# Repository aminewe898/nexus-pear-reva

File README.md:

# NEXUS PEAR REV A — pear pressure

**DO NOT ORDER — engineering review submission.** Revised project: 2026-10-07.

ESP32-S3-WROOM-1U-N16R8, 16 MB flash/8 MB PSRAM, Waveshare 29318 IPS touch display (320 x 480 native / 480 x 320 landscape), two-point FT6336U, digital I2S microphone, stereo MAX98357A modules, 8-ohm speakers, optional microSD, real U.FL-to-RP-SMA external antenna, six ADC keys and bottom USB-C. Carrier 100 x 90 mm, four layers, no battery. Design peak allowance 11.54 W including 20% contingency and an enforced 0.75 W/channel audio cap; no measured peak is claimed.

Open hardware/kicad/nexus-pear-reva/nexus-pear-reva.kicad_pro in KiCad 10. Native schematic, PCB, local symbols and local footprints are included. previews/schematic.pdf is the complete eleven-sheet schematic; previews/pcb-layers.pdf and board-3d.png support review. Manufacturing Gerbers, Excellon drill files, placement CSV, BOM and STEP are under hardware/manufacturing/. Do not submit those as an approved fabrication order.

hardware/BOM_REVA.csv contains exact candidate MPNs; hardware/RFQ_GROUPED.csv groups quantities for procurement. Pricing is incomplete. SUBMISSION.md is the short cover note; docs/ contains the architecture, processor comparison, display/audio/power calculations, pin map, footprint review, sources and first-article test plan. docs/DESIGN_REVIEW_REVA.md identifies every remaining release gate. Native ERC/DRC reports, pad inventory, route metrics and hashed delivery manifest are under validation/.

The revised circuit adds hardware Type-C current qualification and protected input power, removes independently powered 3.3 V peripherals, isolates audio signals and replaces the undocumented display. Corrected manufacturer footprints and routing are in this project's native files. Firmware, physical qualification, complete procurement and enclosure design remain to be completed.

## Publication check — 2026-10-10

A quick source/history credential-pattern scan found no obvious credentials. The delivery manifest was checked against the current checkout: 81 of 84 recorded files match their hashes. The KiCad project file, manufacturing STEP file, and `validation/bom-summary.json` differ from the recorded manifest. This indicates a stale or inconsistent delivery record; those artifacts need reconciliation before release. No CAD regeneration, electrical validation, fabrication approval, or bench testing was performed in this check. The **DO NOT ORDER** status remains in force.

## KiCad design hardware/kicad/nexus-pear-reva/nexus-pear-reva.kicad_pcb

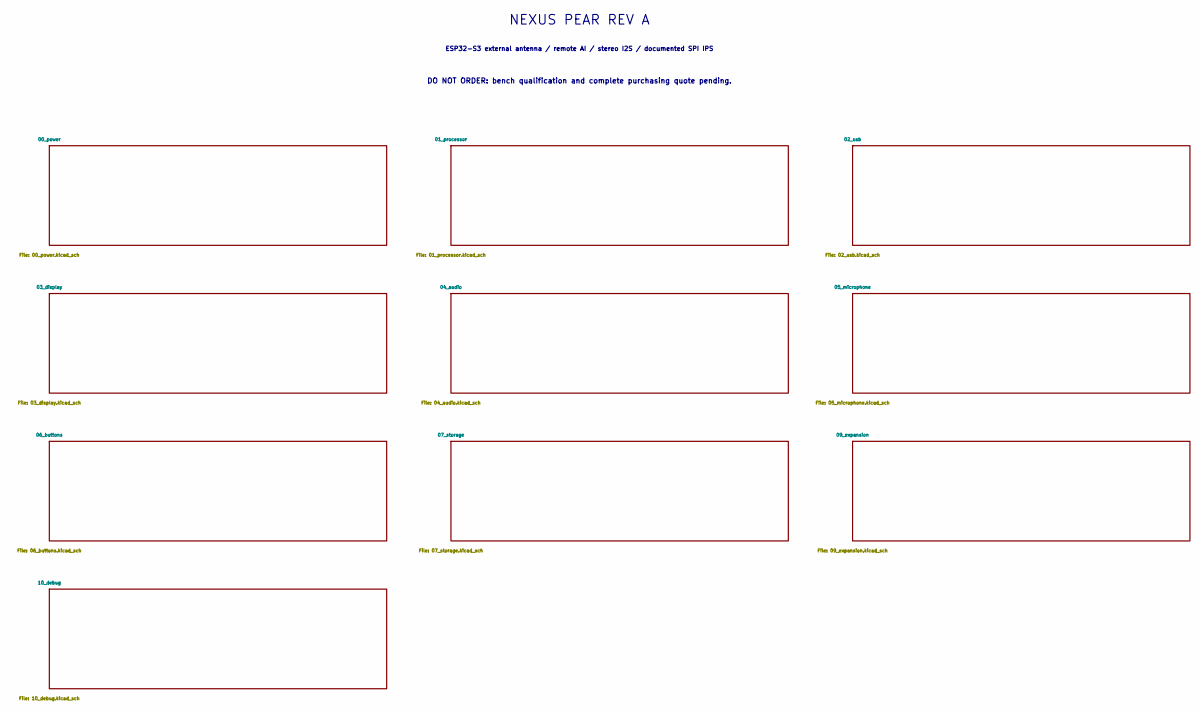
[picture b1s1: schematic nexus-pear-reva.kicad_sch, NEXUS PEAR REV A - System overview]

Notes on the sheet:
NEXUS PEAR REV A
ESP32-S3 external antenna / remote AI / stereo I2S / documented SPI IPS
DO NOT ORDER: bench qualification and complete purchasing quote pending.

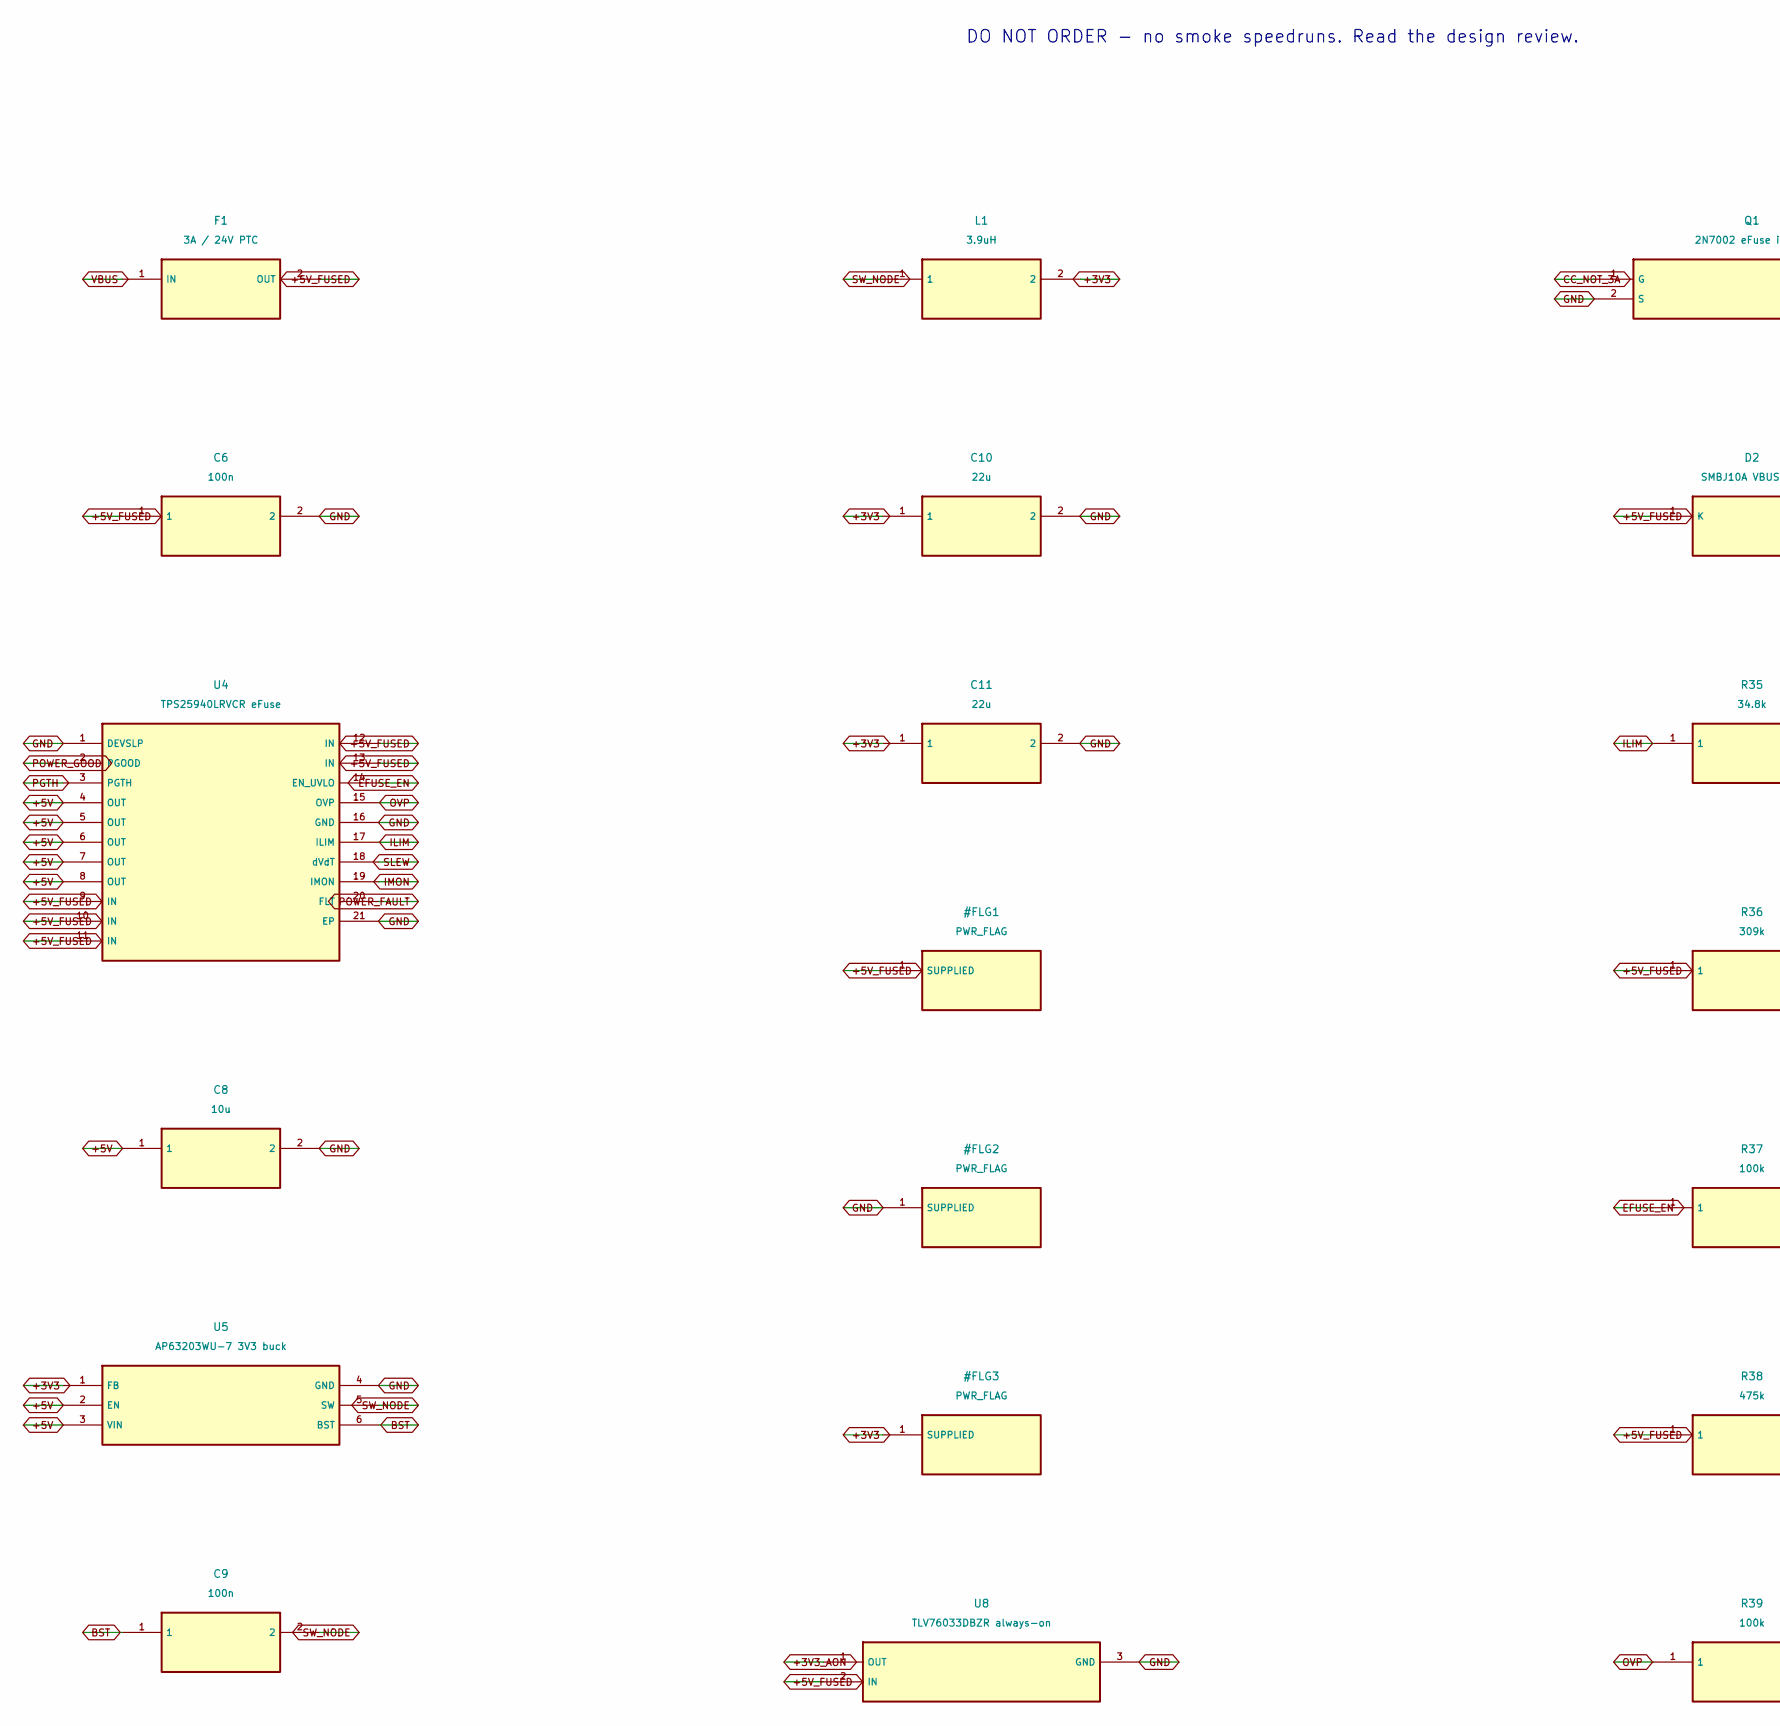
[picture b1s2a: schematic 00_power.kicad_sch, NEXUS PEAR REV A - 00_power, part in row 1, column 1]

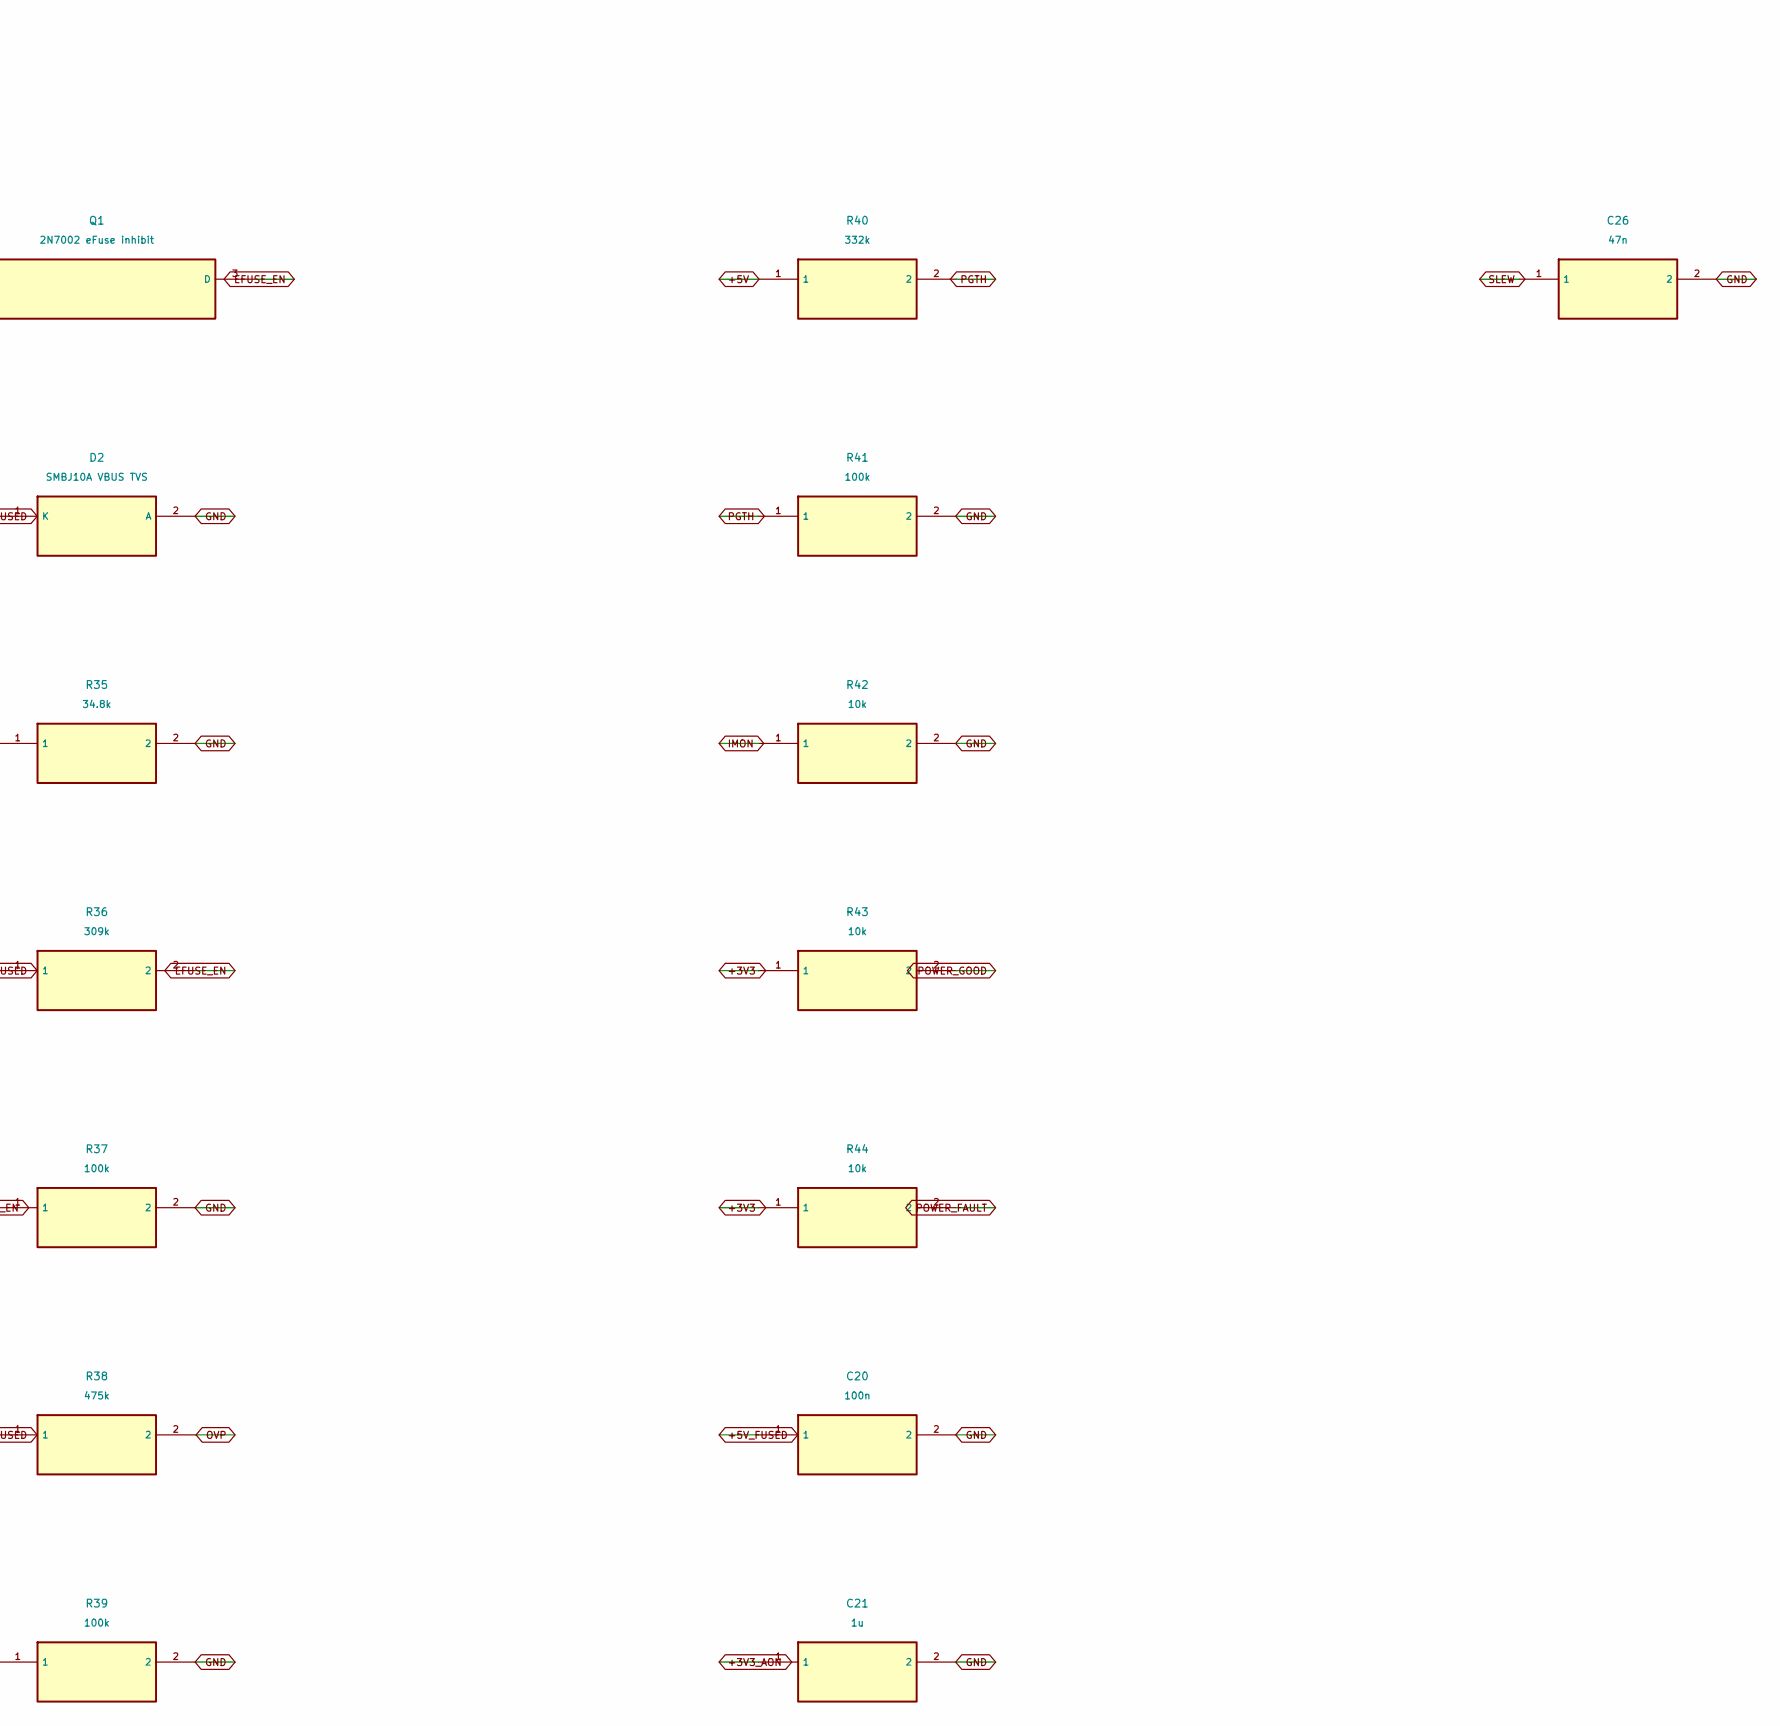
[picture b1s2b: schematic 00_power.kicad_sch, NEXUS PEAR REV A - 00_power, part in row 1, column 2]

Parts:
C6, C9, C20: 100n; C_0805_2012Metric; MPN GRM21BR71H104KA01L
C8: 10u; C_1206_3216Metric; MPN GRM31CR61A106KA01L
C10, C11: 22u; C_1206_3216Metric; MPN GRM31CR61A226KE19L
C21: 1u; C_0805_2012Metric; MPN GRM21BR71A105KA01L
C26: 47n; C_0805_2012Metric; MPN GRM21BR71H473KA01L
D2: SMBJ10A VBUS TVS; D_SMB; MPN SMBJ10A
F1: 3A / 24V PTC; Fuse_1812_4532Metric; MPN 1812L300/24SLER
L1: 3.9uH; L_Bourns-SRN6028; MPN SRN6028C-3R9M
Q1: 2N7002 eFuse inhibit; SOT-23; MPN 2N7002,215
R35: 34.8k; R_0805_2012Metric; MPN RC0805FR-0734K8L
R36: 309k; R_0805_2012Metric; MPN RC0805FR-07309KL
R37, R41: 100k; R_0805_2012Metric; MPN RC0805FR-07100KL
R38: 475k; R_0805_2012Metric; MPN RT0805BRD07475KL
R39: 100k; R_0805_2012Metric; MPN RT0805BRD07100KL
R40: 332k; R_0805_2012Metric; MPN RC0805FR-07332KL
R42, R43, R44: 10k; R_0805_2012Metric; MPN RC0805FR-0710KL
U4: TPS25940LRVCR eFuse; Texas_RVC0020A_WQFN-20-1EP_3x4mm_P0.5mm_EP1.6x2.6mm; MPN TPS25940LRVCR
U5: AP63203WU-7 3V3 buck; TSOT-23-6; MPN AP63203WU-7
U8: TLV76033DBZR always-on; SOT-23; MPN TLV76033DBZR

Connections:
+3V3: C10.1, C11.1, L1.2, R43.1, R44.1, U5.1 (FB); also elsewhere on the board
+3V3_AON: C21.1, U8.1 (OUT); also elsewhere on the board
+5V: C8.1, R40.1, U4.4 (OUT), U4.5 (OUT), U4.6 (OUT), U4.7 (OUT), U4.8 (OUT), U5.2 (EN), U5.3 (VIN); also elsewhere on the board
+5V_FUSED: C6.1, C20.1, D2.1 (K), F1.2 (OUT), R36.1, R38.1, U4.9 (IN), U4.10 (IN), U4.11 (IN), U4.12 (IN), U4.13 (IN), U8.2 (IN); also elsewhere on the board
BST: C9.1, U5.6 (BST)
CC_NOT_3A: Q1.1 (G); also elsewhere on the board
EFUSE_EN: Q1.3 (D), R36.2, R37.1, U4.14 (EN_UVLO)
GND: C6.2, C8.2, C10.2, C11.2, C20.2, C21.2, C26.2, D2.2 (A), Q1.2 (S), R35.2, R37.2, R39.2, R41.2, R42.2, U4.1 (DEVSLP), U4.16 (GND), U4.21 (EP), U5.4 (GND), U8.3 (GND); also elsewhere on the board
ILIM: R35.1, U4.17 (ILIM)
IMON: R42.1, U4.19 (IMON); also elsewhere on the board
OVP: R38.2, R39.1, U4.15 (OVP)
PGTH: R40.2, R41.1, U4.3 (PGTH)
POWER_FAULT: R44.2, U4.20 (FLT)
POWER_GOOD: R43.2, U4.2 (PGOOD)
SLEW: C26.1, U4.18 (dVdT)
SW_NODE: C9.2, L1.1, U5.5 (SW)
VBUS: F1.1 (IN); also elsewhere on the board

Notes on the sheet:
DO NOT ORDER - no smoke speedruns. Read the design review.

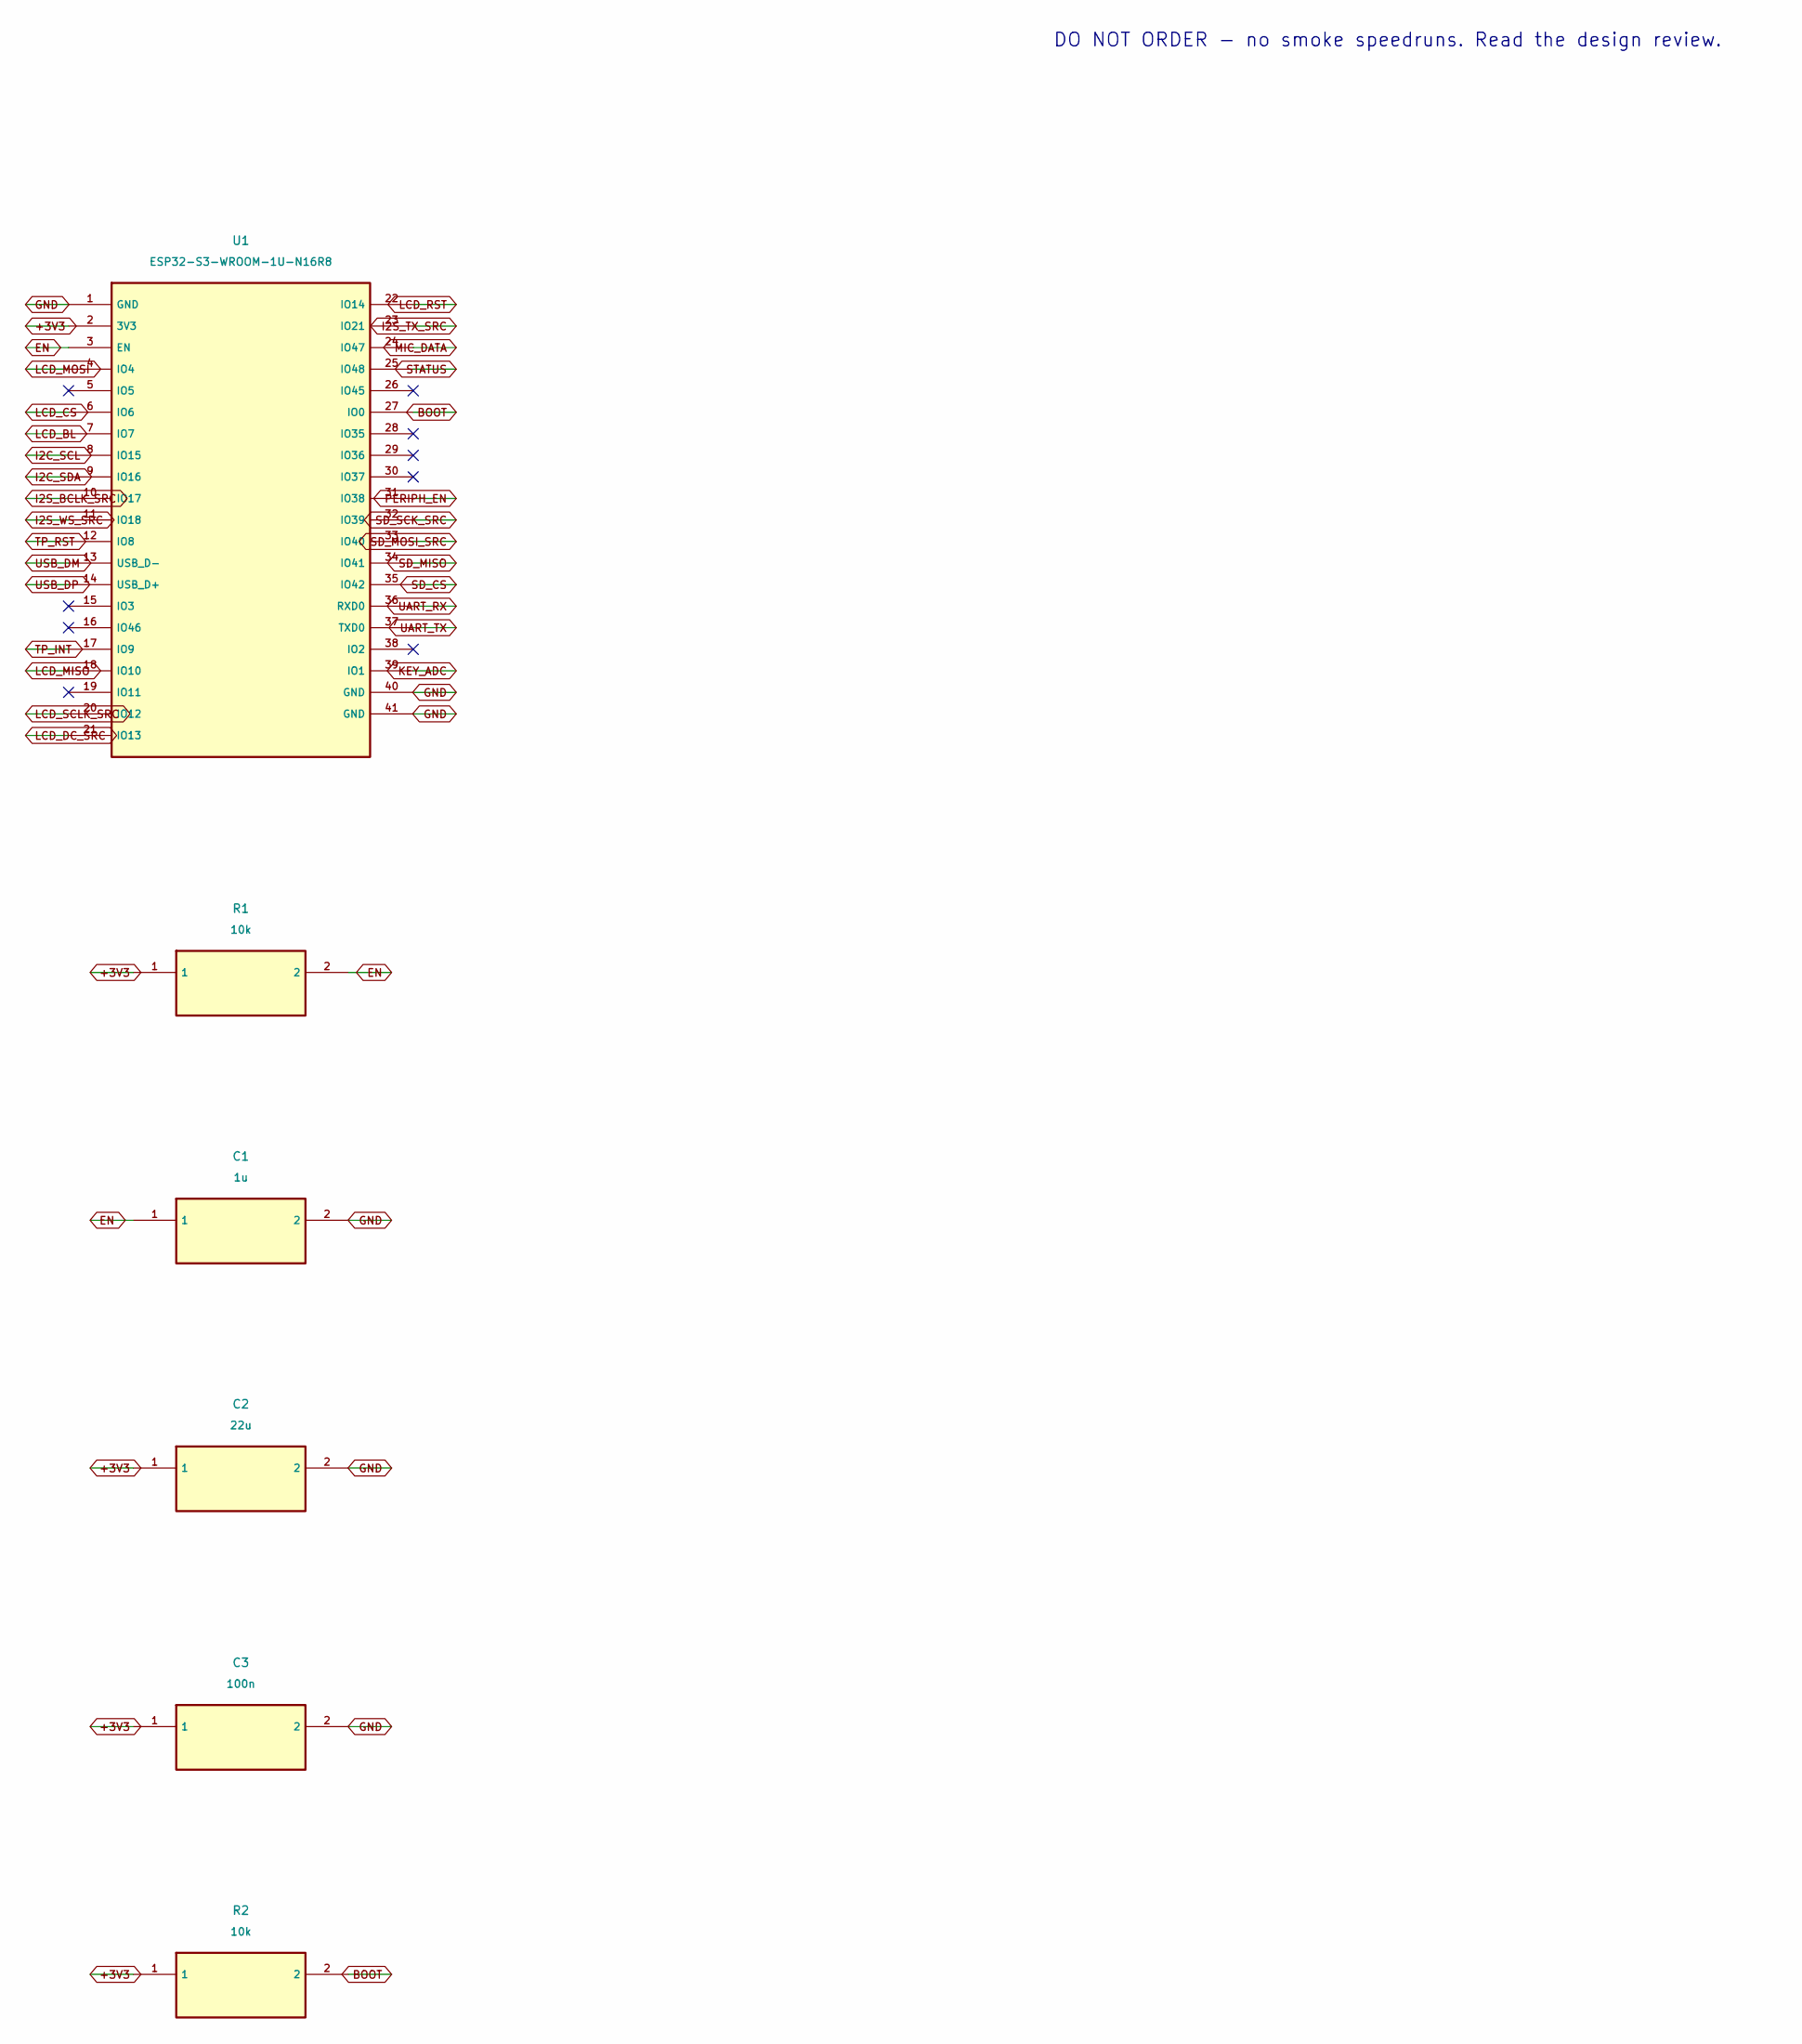
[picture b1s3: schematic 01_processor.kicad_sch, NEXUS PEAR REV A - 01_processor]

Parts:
C1: 1u; C_0805_2012Metric; MPN GRM21BR71A105KA01L
C2: 22u; C_1206_3216Metric; MPN GRM31CR61A226KE19L
C3: 100n; C_0805_2012Metric; MPN GRM21BR71H104KA01L
R1, R2: 10k; R_0805_2012Metric; MPN RC0805FR-0710KL
U1: ESP32-S3-WROOM-1U-N16R8; ESP32-S3-WROOM-1U; MPN ESP32-S3-WROOM-1U-N16R8

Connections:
+3V3: C2.1, C3.1, R1.1, R2.1, U1.2 (3V3); also elsewhere on the board
BOOT: R2.2, U1.27 (IO0); also elsewhere on the board
EN: C1.1, R1.2, U1.3 (EN); also elsewhere on the board
GND: C1.2, C2.2, C3.2, U1.1 (GND), U1.40 (GND), U1.41 (GND); also elsewhere on the board
I2C_SCL: U1.8 (IO15); also elsewhere on the board
I2C_SDA: U1.9 (IO16); also elsewhere on the board
I2S_BCLK_SRC: U1.10 (IO17); also elsewhere on the board
I2S_TX_SRC: U1.23 (IO21); also elsewhere on the board
I2S_WS_SRC: U1.11 (IO18); also elsewhere on the board
KEY_ADC: U1.39 (IO1); also elsewhere on the board
LCD_BL: U1.7 (IO7); also elsewhere on the board
LCD_CS: U1.6 (IO6); also elsewhere on the board
LCD_DC_SRC: U1.21 (IO13); also elsewhere on the board
LCD_MISO: U1.18 (IO10); also elsewhere on the board
LCD_MOSI: U1.4 (IO4); also elsewhere on the board
LCD_RST: U1.22 (IO14); also elsewhere on the board
LCD_SCLK_SRC: U1.20 (IO12); also elsewhere on the board
MIC_DATA: U1.24 (IO47); also elsewhere on the board
PERIPH_EN: U1.31 (IO38); also elsewhere on the board
SD_CS: U1.35 (IO42); also elsewhere on the board
SD_MISO: U1.34 (IO41); also elsewhere on the board
SD_MOSI_SRC: U1.33 (IO40); also elsewhere on the board
SD_SCK_SRC: U1.32 (IO39); also elsewhere on the board
STATUS: U1.25 (IO48); also elsewhere on the board
TP_INT: U1.17 (IO9); also elsewhere on the board
TP_RST: U1.12 (IO8); also elsewhere on the board
UART_RX: U1.36 (RXD0); also elsewhere on the board
UART_TX: U1.37 (TXD0); also elsewhere on the board
USB_DM: U1.13 (USB_D-); also elsewhere on the board
USB_DP: U1.14 (USB_D+); also elsewhere on the board

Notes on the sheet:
DO NOT ORDER - no smoke speedruns. Read the design review.

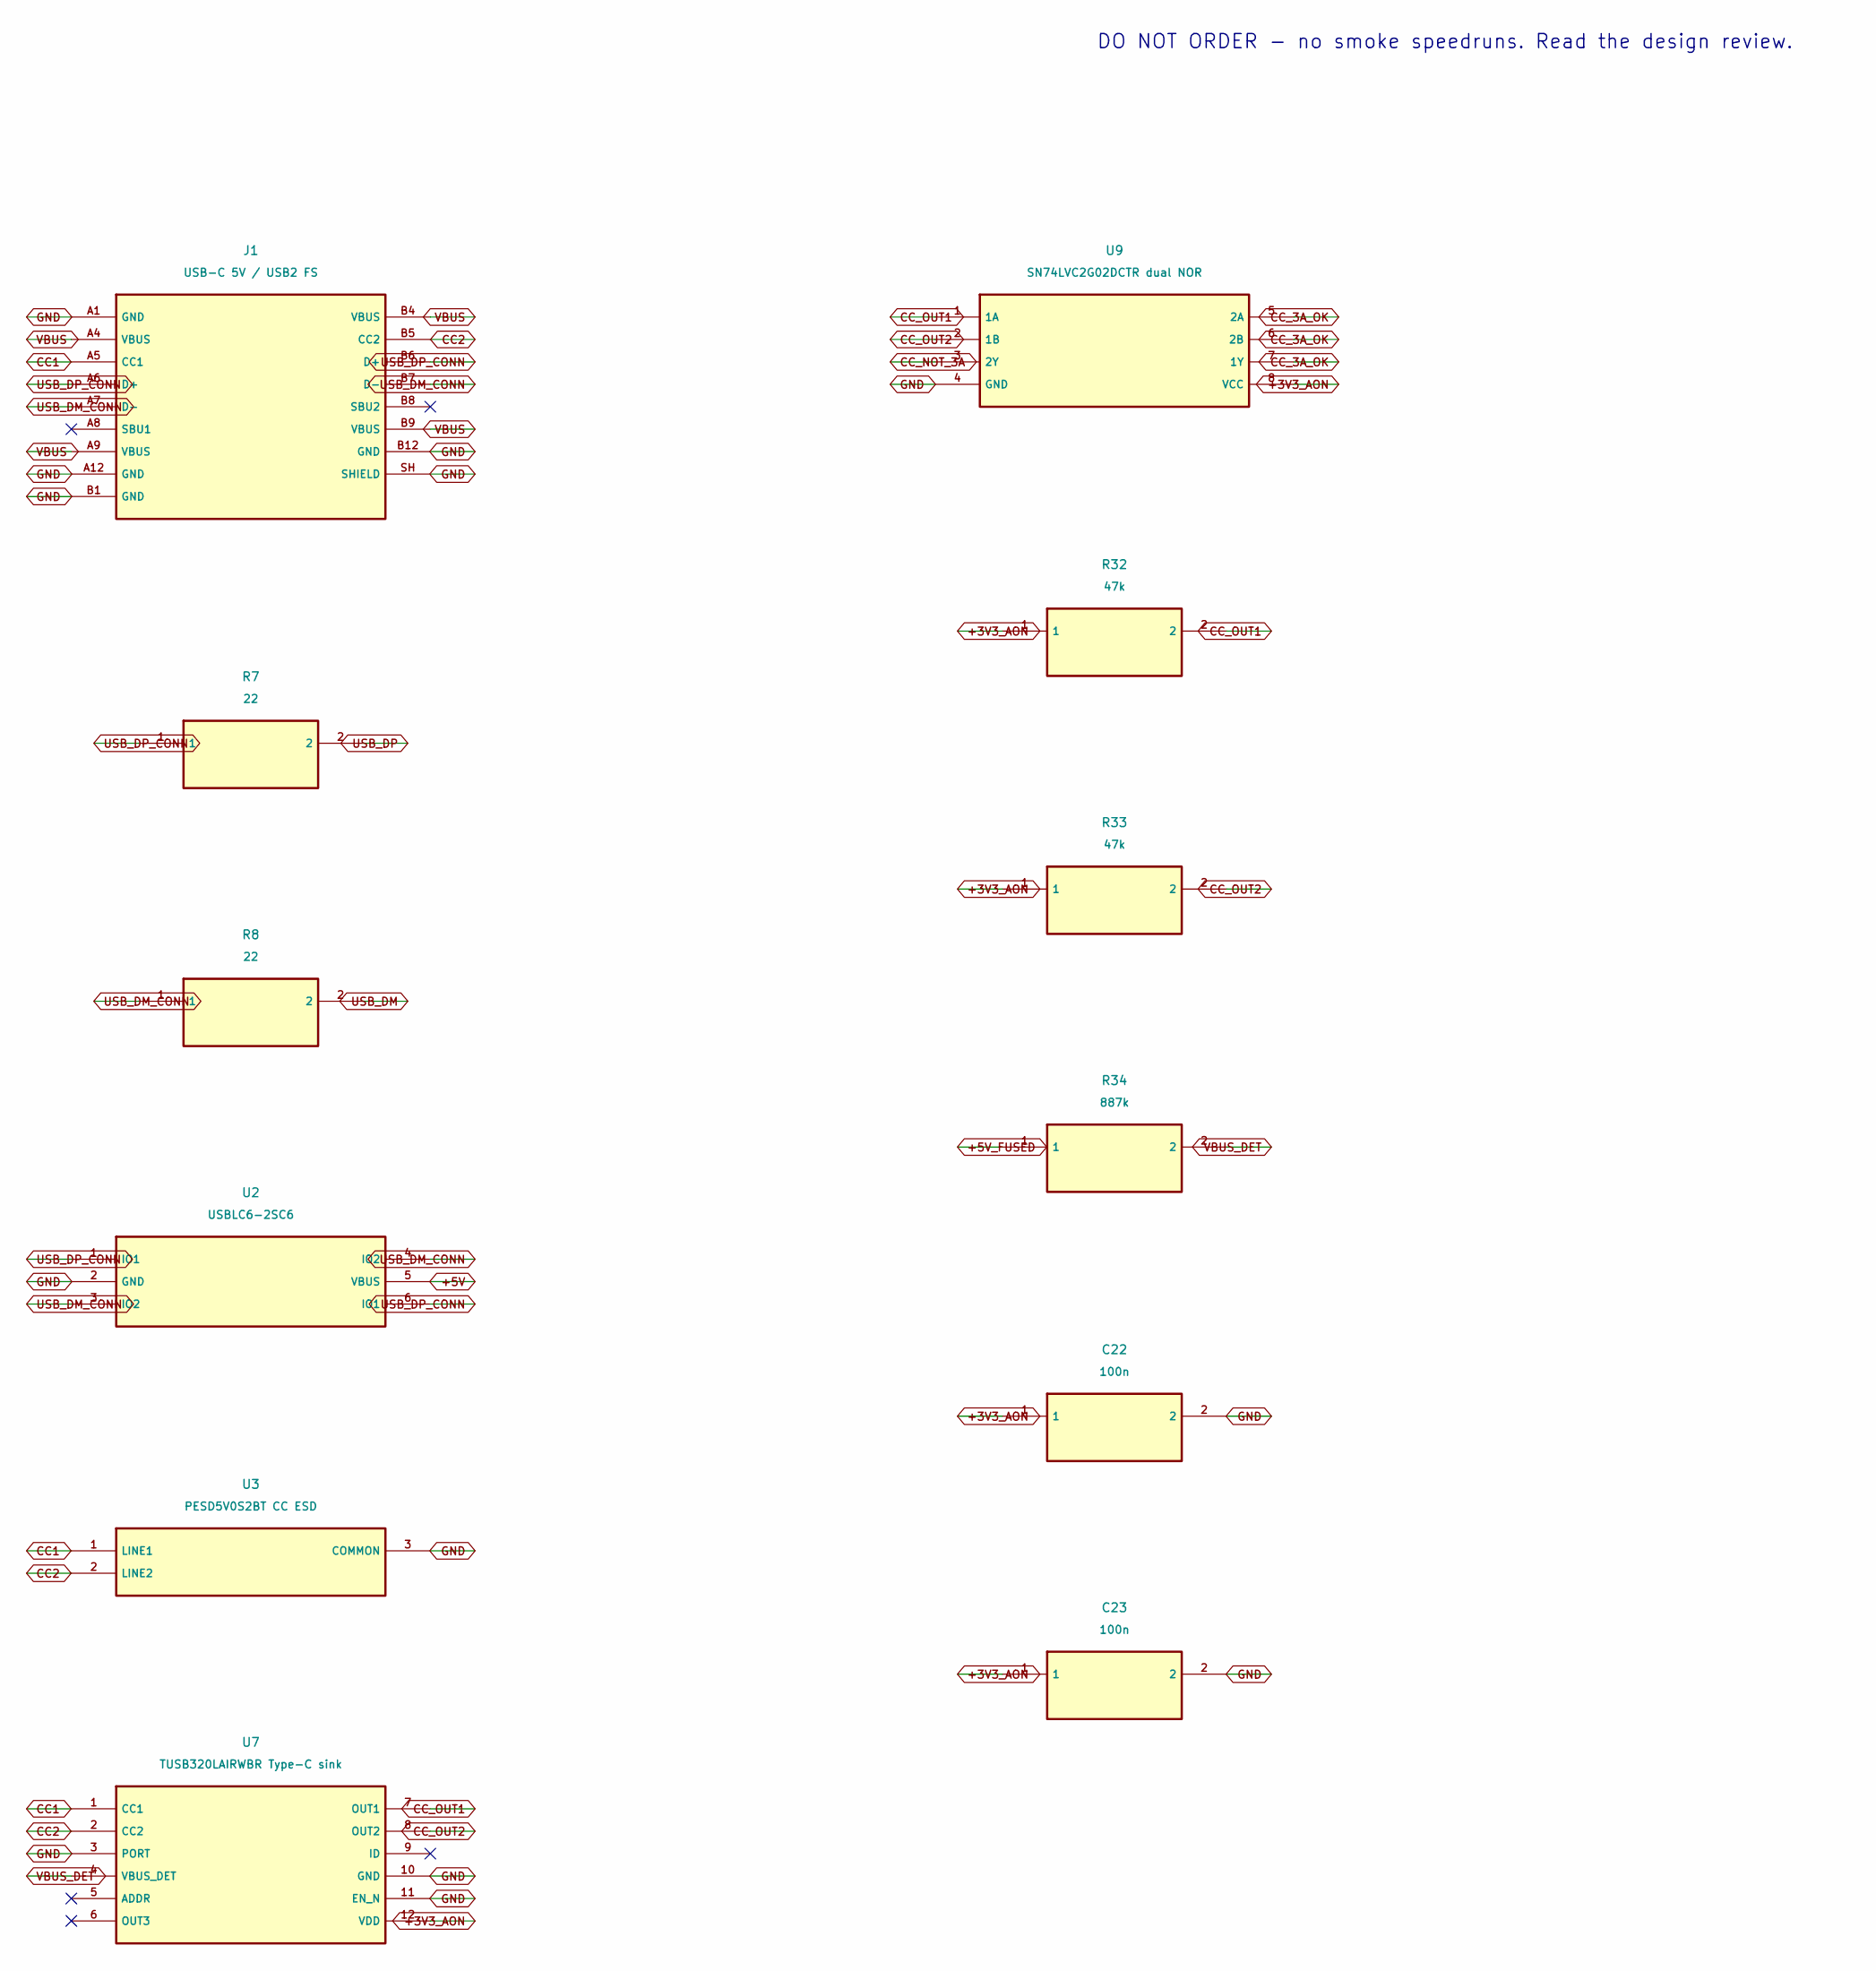
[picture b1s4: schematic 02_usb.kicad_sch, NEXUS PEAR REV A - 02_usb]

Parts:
C22, C23: 100n; C_0805_2012Metric; MPN GRM21BR71H104KA01L
J1: USB-C 5V / USB2 FS; USB_C_Receptacle_GCT_USB4105-xx-A_16P_TopMnt_Horizontal; MPN USB4105-GF-A
R7, R8: 22; R_0805_2012Metric; MPN RC0805FR-0722RL
R32, R33: 47k; R_0805_2012Metric; MPN RC0805FR-0747KL
R34: 887k; R_0805_2012Metric; MPN RC0805FR-07887KL
U2: USBLC6-2SC6; SOT-23-6; MPN USBLC6-2SC6
U3: PESD5V0S2BT CC ESD; SOT-23; MPN PESD5V0S2BT,215
U7: TUSB320LAIRWBR Type-C sink; Texas_X2QFN-12_1.6x1.6mm_P0.4mm; MPN TUSB320LAIRWBR
U9: SN74LVC2G02DCTR dual NOR; SSOP-8_2.95x2.8mm_P0.65mm; MPN SN74LVC2G02DCTR

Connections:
+3V3_AON: C22.1, C23.1, R32.1, R33.1, U7.12 (VDD), U9.8 (VCC); also elsewhere on the board
+5V: U2.5 (VBUS); also elsewhere on the board
+5V_FUSED: R34.1; also elsewhere on the board
CC1: J1.A5 (CC1), U3.1 (LINE1), U7.1 (CC1)
CC2: J1.B5 (CC2), U3.2 (LINE2), U7.2 (CC2)
CC_3A_OK: U9.5 (2A), U9.6 (2B), U9.7 (1Y); also elsewhere on the board
CC_NOT_3A: U9.3 (2Y); also elsewhere on the board
CC_OUT1: R32.2, U7.7 (OUT1), U9.1 (1A)
CC_OUT2: R33.2, U7.8 (OUT2), U9.2 (1B)
GND: C22.2, C23.2, J1.A1 (GND), J1.A12 (GND), J1.B1 (GND), J1.B12 (GND), J1.SH (SHIELD), U2.2 (GND), U3.3 (COMMON), U7.3 (PORT), U7.10 (GND), U7.11 (EN_N), U9.4 (GND); also elsewhere on the board
USB_DM: R8.2; also elsewhere on the board
USB_DM_CONN: J1.A7 (D-), J1.B7 (D-), R8.1, U2.3 (IO2), U2.4 (IO2)
USB_DP: R7.2; also elsewhere on the board
USB_DP_CONN: J1.A6 (D+), J1.B6 (D+), R7.1, U2.1 (IO1), U2.6 (IO1)
VBUS: J1.A4 (VBUS), J1.A9 (VBUS), J1.B4 (VBUS), J1.B9 (VBUS); also elsewhere on the board
VBUS_DET: R34.2, U7.4 (VBUS_DET)

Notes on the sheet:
DO NOT ORDER - no smoke speedruns. Read the design review.
